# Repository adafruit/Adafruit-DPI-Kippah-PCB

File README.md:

## Adafruit DPI Kippah PCB

&nbsp; 
<br/>
Click the image or links below to go to a specific product in the Adafruit shop.

PCB files for the Adafruit Adafruit DPI Display Kippah for Raspberry PI. Format is EagleCAD schematic and board layout
* TFT & Resistive Touch support https://www.adafruit.com/product/2453
* TFT Display Support Only https://www.adafruit.com/product/2454

### DESCRIPTION
A TFT panel connected to a Raspberry Pi without the use of an HDMI decoder? What is this sorcery??? It's the DPI Kippah from Adafruit! This HAT-like* board snaps onto a Raspberry Pi B+, A+, Pi 2, Pi 3 or Zero and with a little software configuration, allows you to have what normally would go out the HDMI port come up on a nice little flat screen. *Its not technically a HAT due to the lack of an on-board EEPROM, but its the same shape as a Pi HAT and its a covering of sorts, so we call it a kippah

This is the Kippah with resistive touch support. If you don't need a touchscreen then here's our super low-cost version of the Kippah without the USB touchscreen capability.

Compared to our lovely HDMI backpacks, you don't have the extra cost or expense of an HDMI encoder/decoder. And you get a nice ultra-fast 18-bit color display with optional touch support. We tested it and it works great with our 5" and 7" displays at 800x480. This display is 'native' so it gets all the graphics accelleration capabilities, instant refresh, etc. you would get from an HDMI display

OK so, exciting right? But, what's the catch? The catch is this add on board uses nearly every pin available on the Raspberry Pi and those pins are hardcoded, they cannot be moved or rearranged. The pins used are GPIO 2 through 21 inclusive. That means you don't get the UART RX/TX pins (no console cable) and you don't get the standard user I2C pins, the EEPROM I2C pins, or hardware SPI pins. You do get to use pins #22, #23, #24, #25, #26 and #27, and the USB ports are fine to use too.

The other catch is that this display replaces the HDMI/NTSC output, so you can't have the DPI HAT and HDMI working at once, nor can you 'flip' between the two.

Also, there's no PWM's available so you can't have precision backlight control unless you somehow rig up an external PWM generator with a 555 or something. Finally, we did test this setup with a straight-up Raspbian and after the software installs, it works great. However, we don't guarantee it will work with any other Raspberry Pi operating system or setup.

That said, if you dont need all of the Pi GPIO, its very easy to add a high quality display. Pick and choose whether you want a touch-screen or not, then choose the size of the display - 5" or 7" is best. You can also grab an FPC extension board and extend the display away from the Pi. For power-users, this is a very nice little accessory

Comes as one fully assembled and tested DPI Kippah circuit board. You may need a soldering iron to adjust the backlight by soldering closed a PCB jumper (check the tutorial on this).TFT display, USB micro-B cable, FPC extension cable, bent wire stand, and Raspberry Pi not included (but we do carry them in the shop!) Check out our tutorial on how to install the device tree overlay and configure the backlight

### License

Adafruit invests time and resources providing this open source design, please support Adafruit and open-source hardware by purchasing products from [Adafruit.com](https://www.adafruit.com)!

Creative Commons Attribution, Share-Alike license, check license.txt for more information All text above must be included in any redistribution - 
See license.txt for more information.

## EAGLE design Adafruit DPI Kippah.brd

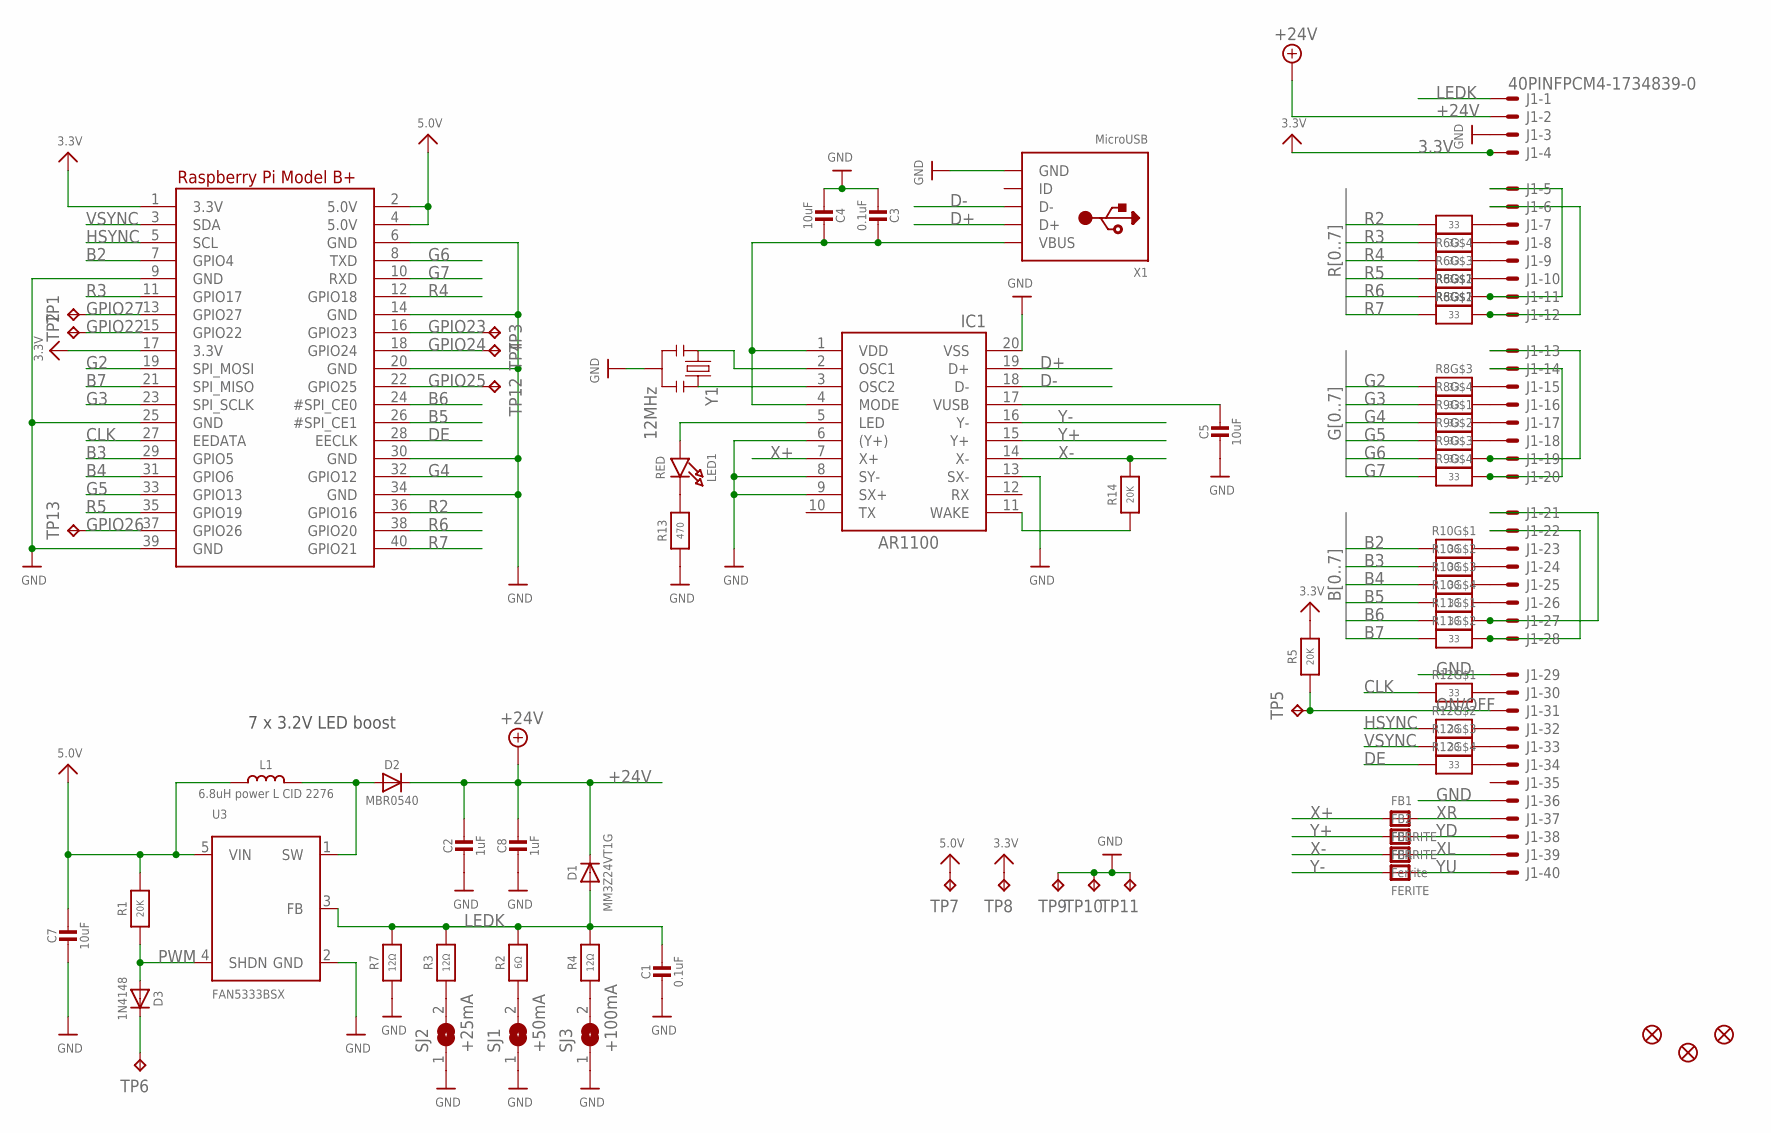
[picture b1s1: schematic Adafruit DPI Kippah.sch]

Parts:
C1, C3: 0.1uF; 0805-NO
C2: 1uF; _0805MP
C4, C5, C7: 10uF; 0805-NO
C8: 1uF; 0805-NO
D1: MM3Z24VT1G; SMADIODE
D2: MBR0540; SOD-123
D3: 1N4148; SOD-323
FB1, FB2: FERRITE; _0805MP
FB3: Ferrite; _0805MP
FB4: FERITE; _0805MP
FID1, FID2, FID3: FIDUCIAL""; FIDUCIAL_1MM
IC1: AR1100_SSOP; TSSOP20-5.3MMBODY
J1: 40PINFPCM4-1734839-0; 4-1734839-0
L1: 6.8uH power L CID 2276; INDUCTOR_5X5MM_NR5040_NOTHERMALS
LED1: RED; CHIPLED_0805_NOOUTLINE
R1, R14: 20K; 0805-NO
R2: 6Ω; 0805-NO
R3, R4, R7: 12Ω; 0805-NO
R5: 20K; _0805MP
R6, R8, R9, R10, R11, R12: 33; RESPACK_4X0603
R13: 470; 0805-NO
RPI1: RASPBERRYPI_BPLUS-SMT+SLOTS; PI_HAT_SMT_SLOTS
SJ1: +50mA; SOLDERJUMPER_ARROW_NOPASTE
SJ2: +25mA; SOLDERJUMPER_ARROW_NOPASTE
SJ3: +100mA; SOLDERJUMPER_ARROW_NOPASTE
TP1, TP2, TP3, TP4, TP5, TP6, TP7, TP8, TP9, TP10, TP11, TP12, TP13: TPTP15SQ; TP15SQ
U3: FAN5333BSX; SOT23-5@1
X1: MicroUSB; 4UCONN_20329
Y1: 12MHz; RESONATOR-SMD

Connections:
3.3V: J1.4 (MS), R5.2, RPI1.1 (3.3V), RPI1.17 (3.3V), TP8.TP
5.0V: C7.1, L1.P$1 (1), R1.2, RPI1.2 (5.0V), RPI1.4 (5.0V), TP7.TP, U3.5 (VIN)
+24V: C2.1, C8.1, D1.C, D2.C, J1.2 (MS)
B2: R10.1, RPI1.7 (GPIO4)
B3: R10.2 (1), RPI1.29 (GPIO5)
B4: R10.3 (1), RPI1.31 (GPIO6)
B5: R10.4 (1), RPI1.26 (#SPI_CE1)
B6: R11.1, RPI1.24 (#SPI_CE0)
B7: R11.2 (1), RPI1.21 (SPI_MISO)
CLK: R12.1, RPI1.27 (EEDATA)
D+: IC1.19 (D+), X1.D+
D-: IC1.18 (D-), X1.D-
DE: R12.4 (1), RPI1.28 (EECLK)
G2: R8.3 (1), RPI1.19 (SPI_MOSI)
G3: R8.4 (1), RPI1.23 (SPI_SCLK)
G4: R9.1, RPI1.32 (GPIO12)
G5: R9.2 (1), RPI1.33 (GPIO13)
G6: R9.3 (1), RPI1.8 (TXD)
G7: R9.4 (1), RPI1.10 (RXD)
GND: C1.2, C2.2, C3.2, C4.2, C5.2, C7.2, C8.2, IC1.6 ((Y+)), IC1.8 (SY-), IC1.9 (SX+), IC1.13 (SX-), IC1.20 (VSS), J1.3 (MS), J1.29 (MS), J1.36 (MS), R7.1, R13.1, RPI1.6 (GND), RPI1.9 (GND), RPI1.14 (GND), RPI1.20 (GND), RPI1.25 (GND), RPI1.30 (GND), RPI1.34 (GND), RPI1.39 (GND), SJ1.1, SJ2.1, SJ3.1, TP9.TP, TP10.TP, TP11.TP, U3.2 (GND), X1.BASE@1 (GND), X1.BASE@2 (GND), X1.GND, X1.SPRT@1 (GND), X1.SPRT@2 (GND), X1.SPRT@3 (GND), X1.SPRT@4 (GND), Y1.2
GPIO22: RPI1.15 (GPIO22), TP2.TP
GPIO23: RPI1.16 (GPIO23), TP3.TP
GPIO24: RPI1.18 (GPIO24), TP4.TP
GPIO25: RPI1.22 (GPIO25), TP12.TP
GPIO26: RPI1.37 (GPIO26), TP13.TP
GPIO27: RPI1.13 (GPIO27), TP1.TP
HSYNC: R12.2 (1), RPI1.5 (SCL)
LEDK: C1.1, D1.A, J1.1 (MSV), R2.2, R3.2, R4.2, R7.2, U3.3 (FB)
unnamed: R2.1, SJ1.2
unnamed: R3.1, SJ2.2
unnamed: R4.1, SJ3.2
unnamed: J1.6 (MS), J1.12 (MS), R8.7 (2)
unnamed: D2.A, L1.P$2 (2), U3.1 (SW)
unnamed: J1.5 (MS), J1.11 (MS), R8.8 (2)
unnamed: J1.10 (MS), R6.1
unnamed: J1.9 (MS), R6.2 (1)
unnamed: J1.8 (MS), R6.3 (1)
unnamed: J1.7 (MS), R6.4 (1)
unnamed: J1.15 (MS), R8.6 (2)
unnamed: J1.16 (MS), R8.5 (2)
unnamed: J1.17 (MS), R9.8 (2)
unnamed: J1.18 (MS), R9.7 (2)
unnamed: J1.13 (MS), J1.19 (MS), R9.6 (2)
unnamed: J1.14 (MS), J1.20 (MS), R9.5 (2)
unnamed: J1.23 (MS), R10.8 (2)
unnamed: J1.24 (MS), R10.7 (2)
unnamed: J1.25 (MS), R10.6 (2)
unnamed: J1.26 (MS), R10.5 (2)
unnamed: J1.21 (MS), J1.27 (MS), R11.8 (2)
unnamed: J1.22 (MS), J1.28 (MS), R11.7 (2)
unnamed: J1.30 (MS), R12.8 (2)
unnamed: J1.32 (MS), R12.7 (2)
unnamed: J1.33 (MS), R12.6 (2)
unnamed: J1.34 (MS), R12.5 (2)
unnamed: D3.C, TP6.TP
unnamed: IC1.5 (LED), LED1.A
unnamed: LED1.C, R13.2
unnamed: IC1.11 (WAKE), R14.1
unnamed: IC1.3 (OSC2), Y1.3
unnamed: IC1.2 (OSC1), Y1.1
ON/OFF: J1.31 (MS), R5.1, TP5.TP
PWM: D3.A, R1.1, U3.4 (SHDN)
R2: R6.5 (2), RPI1.36 (GPIO16)
R3: R6.6 (2), RPI1.11 (GPIO17)
R4: R6.7 (2), RPI1.12 (GPIO18)
R5: R6.8 (2), RPI1.35 (GPIO19)
R6: R8.1, RPI1.38 (GPIO20)
R7: R8.2 (1), RPI1.40 (GPIO21)
VBUS: C3.1, C4.1, IC1.1 (VDD), IC1.4 (MODE), X1.VBUS
VSYNC: R12.3 (1), RPI1.3 (SDA)
VUSB: C5.1, IC1.17 (VUSB)
X+: FB1.1, IC1.7 (X+)
X-: FB3.1, IC1.14 (X-), R14.2
XL: FB3.2, J1.39 (MS)
XR: FB1.2, J1.37 (MS)
Y+: FB2.1, IC1.15 (Y+)
Y-: FB4.1, IC1.16 (Y-)
YD: FB2.2, J1.38 (MS)
YU: FB4.2, J1.40 (MS)

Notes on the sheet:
7 x 3.2V LED boost

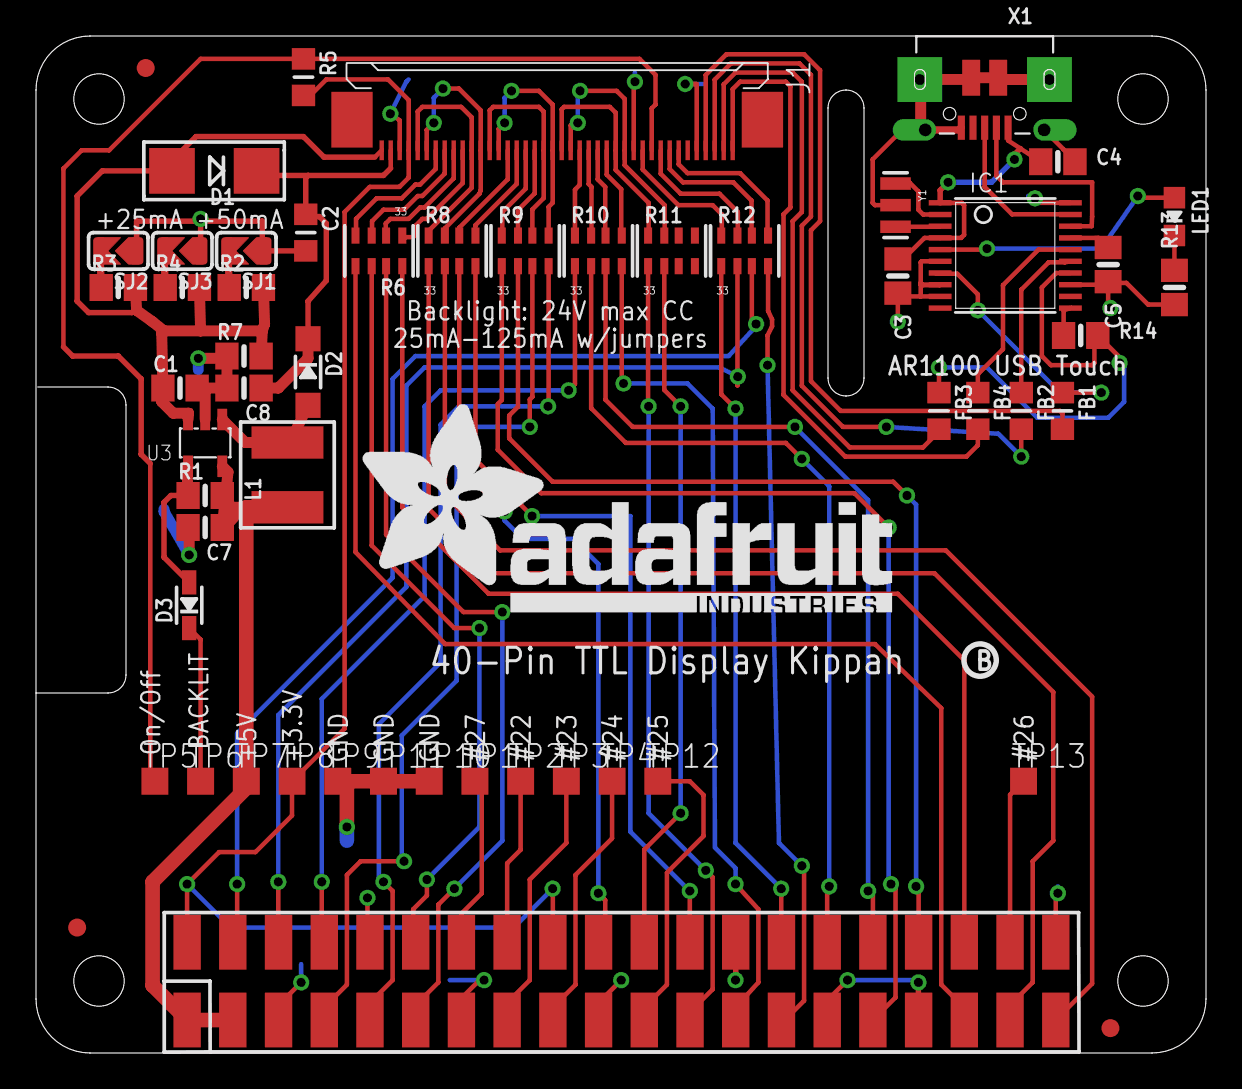
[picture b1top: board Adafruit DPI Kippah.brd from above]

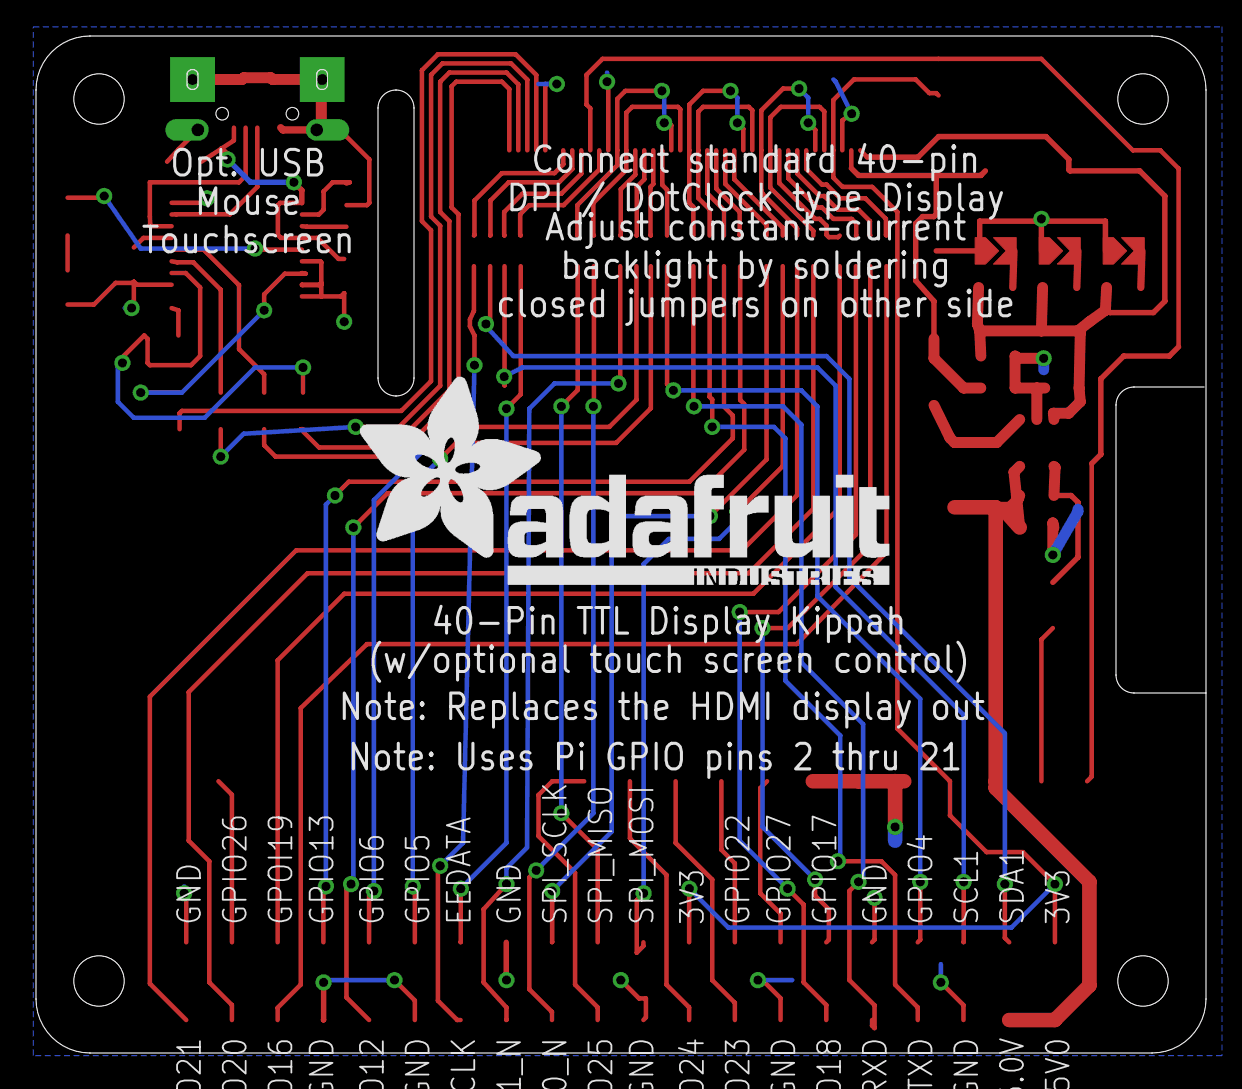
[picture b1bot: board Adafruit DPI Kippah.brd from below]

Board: 2 copper layers, 65.0 x 56.5 mm, 58 parts (2 on the bottom side), 79 nets.

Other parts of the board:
U$30, U$31: ADAFRUIT_TEXT_30MM
U$32: PCBFEAT-REV-040

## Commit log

2016-10-01 init

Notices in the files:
parts and their libraries:
SparkFun: Licensing: CC v3.0 Share-Alike You are welcome to use this library for commercial purposes.
